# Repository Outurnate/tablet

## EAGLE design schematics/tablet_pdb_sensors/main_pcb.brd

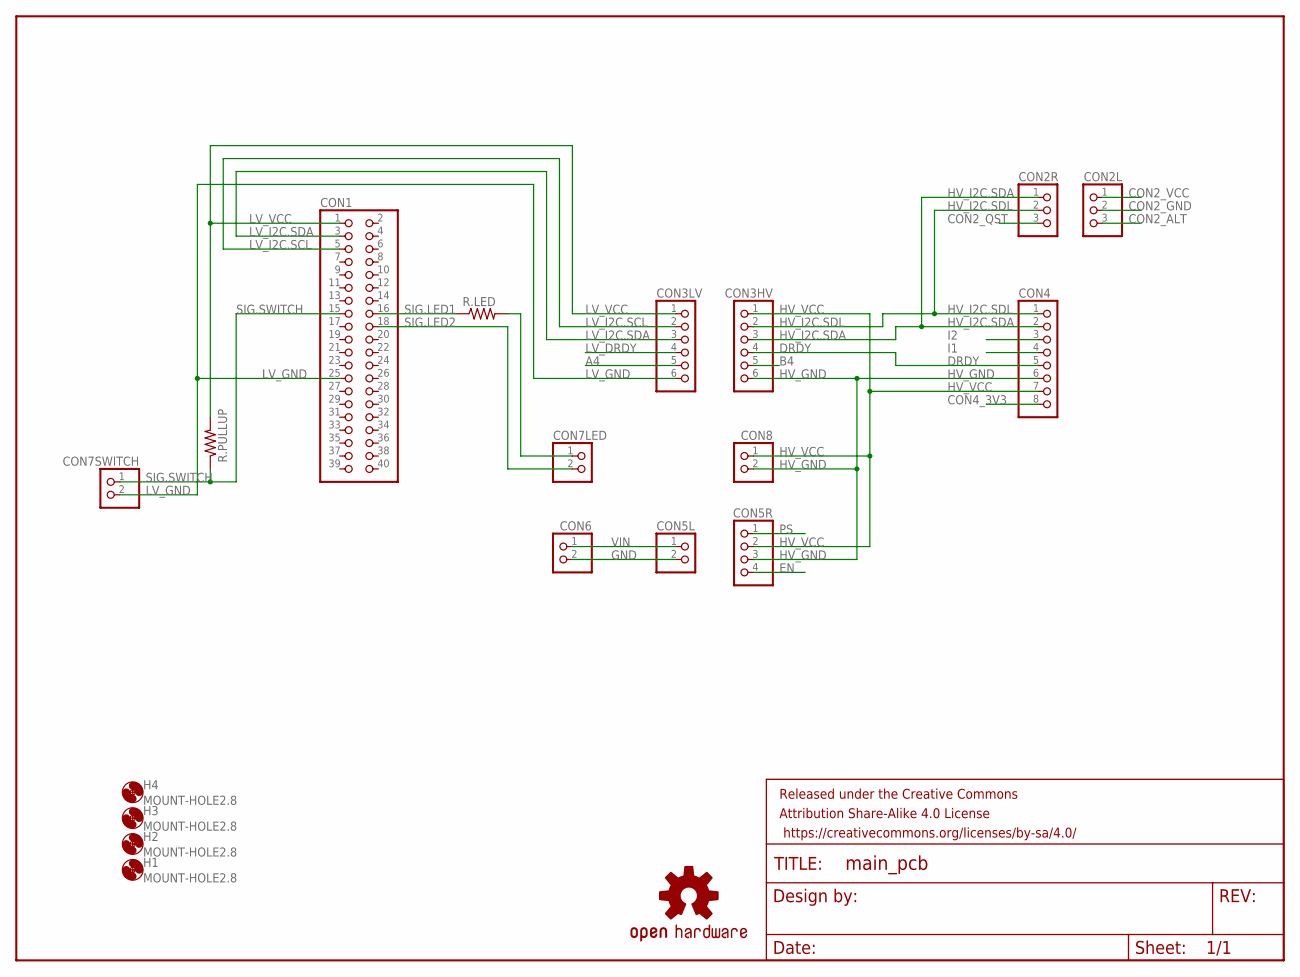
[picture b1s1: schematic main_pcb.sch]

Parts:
CON1: PINHD-2X20; 2X20
CON2L, CON2R: PINHD-1X3; 1X03
CON3HV, CON3LV: PINHD-1X6; 1X06
CON4: PINHD-1X8; 1X08
CON5L, CON6, CON7LED, CON7SWITCH, CON8: PINHD-1X2; 1X02
CON5R: PINHD-1X4; 1X04
FRAME1: FRAME-LETTER; CREATIVE_COMMONS
H1, H2, H3, H4: MOUNT-HOLE2.8; 2,8
LOGO1: OSHW-LOGOL; OSHW-LOGO-L
R.LED, R.PULLUP: R-US_0204/2V; 0204V

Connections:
A4: CON3LV.5
B4: CON3HV.5
CON2_ALT: CON2L.3
CON2_GND: CON2L.2
CON2_QST: CON2R.3
CON2_VCC: CON2L.1
CON4_3V3: CON4.8
DRDY: CON3HV.4, CON4.5
EN: CON5R.4
GND: CON5L.2, CON6.2
HV_GND: CON3HV.6, CON4.6, CON5R.3, CON8.2
HV_I2C.SDA: CON2R.1, CON3HV.3, CON4.2
HV_I2C.SDL: CON2R.2, CON3HV.2, CON4.1
HV_VCC: CON3HV.1, CON4.7, CON5R.2, CON8.1
I1: CON4.4
I2: CON4.3
LV_DRDY: CON3LV.4
LV_GND: CON1.25, CON3LV.6, CON7SWITCH.2
LV_I2C.SCL: CON1.5, CON3LV.2
LV_I2C.SDA: CON1.3, CON3LV.3
LV_VCC: CON1.1, CON3LV.1, R.PULLUP.2
unnamed: CON7LED.1, R.LED.2
PS: CON5R.1
SIG.LED1: CON1.16, R.LED.1
SIG.LED2: CON1.18, CON7LED.2
SIG.SWITCH: CON1.15, CON7SWITCH.1, R.PULLUP.1
VIN: CON5L.1, CON6.1

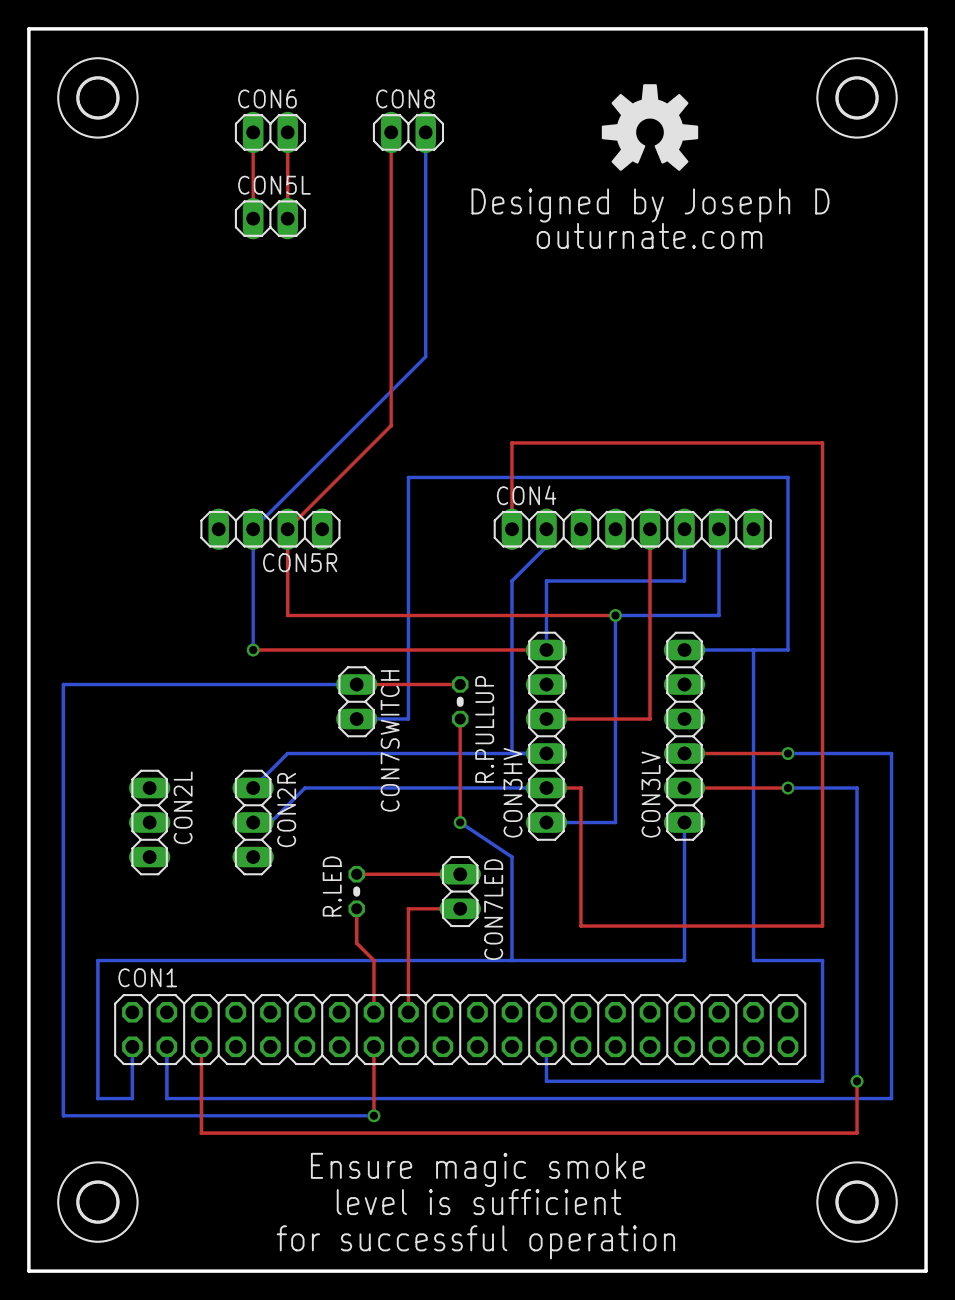
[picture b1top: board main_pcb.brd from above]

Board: 2 copper layers, 66.0 x 91.4 mm, 20 parts (0 on the bottom side), 15 nets.

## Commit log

2015-05-17 how do i eagle
2015-05-17 Cleanup
2015-05-17 Schematic+gathered resources
2015-05-17 more drawings
2015-05-17 Fixed line endings in PDFs
2015-05-17 Recommit
2015-05-17 I am not a smart man
2015-05-17 Real pdfs!
2015-05-17 Pinta is sort of like ms paint, I guess
2015-05-17 A little cleaning
2015-05-17 Rearrange
2015-05-17 Wired up fuel cell and charger
2015-05-18 Swap odroid for rpi2
2015-05-21 Started image build script
2015-05-26 Updated rpi drawing
2015-05-30 Completed schematic

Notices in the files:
parts and their libraries:
SparkFun-Aesthetics: Licensing: Creative Commons ShareAlike 4.0 International - https://creativecommons.org/licenses/by-sa/4.0
SparkFun-Aesthetics: Released under the Creative Commons Attribution Share-Alike 4.0 License
SparkFun-Aesthetics: https://creativecommons.org/licenses/by-sa/4.0
